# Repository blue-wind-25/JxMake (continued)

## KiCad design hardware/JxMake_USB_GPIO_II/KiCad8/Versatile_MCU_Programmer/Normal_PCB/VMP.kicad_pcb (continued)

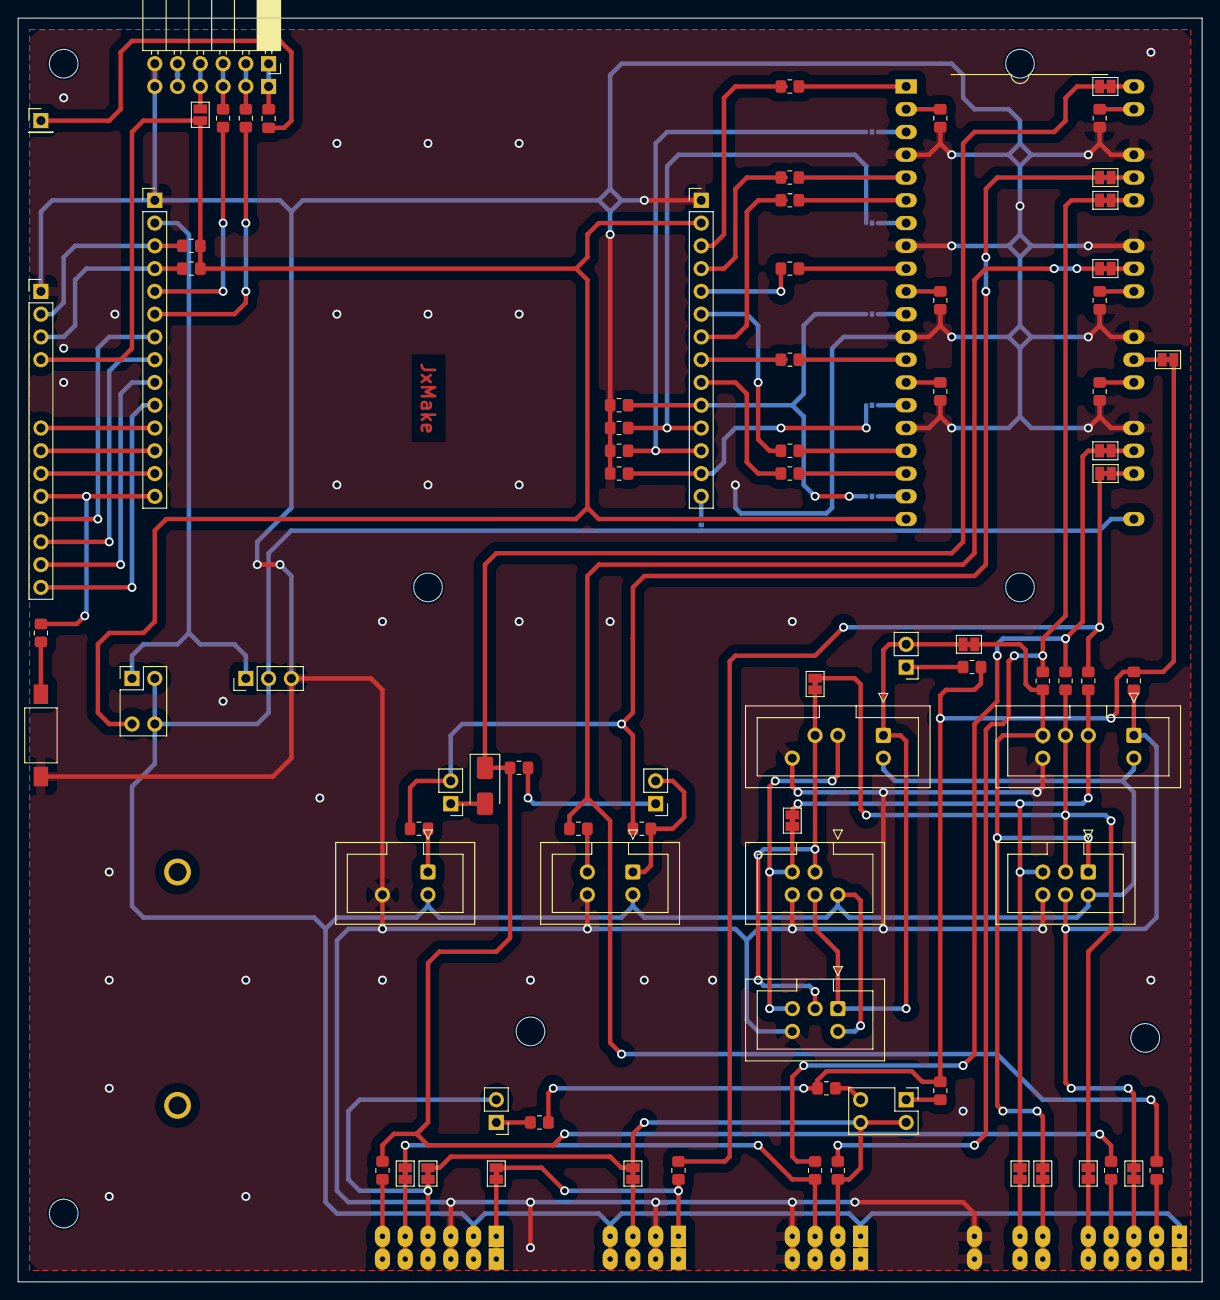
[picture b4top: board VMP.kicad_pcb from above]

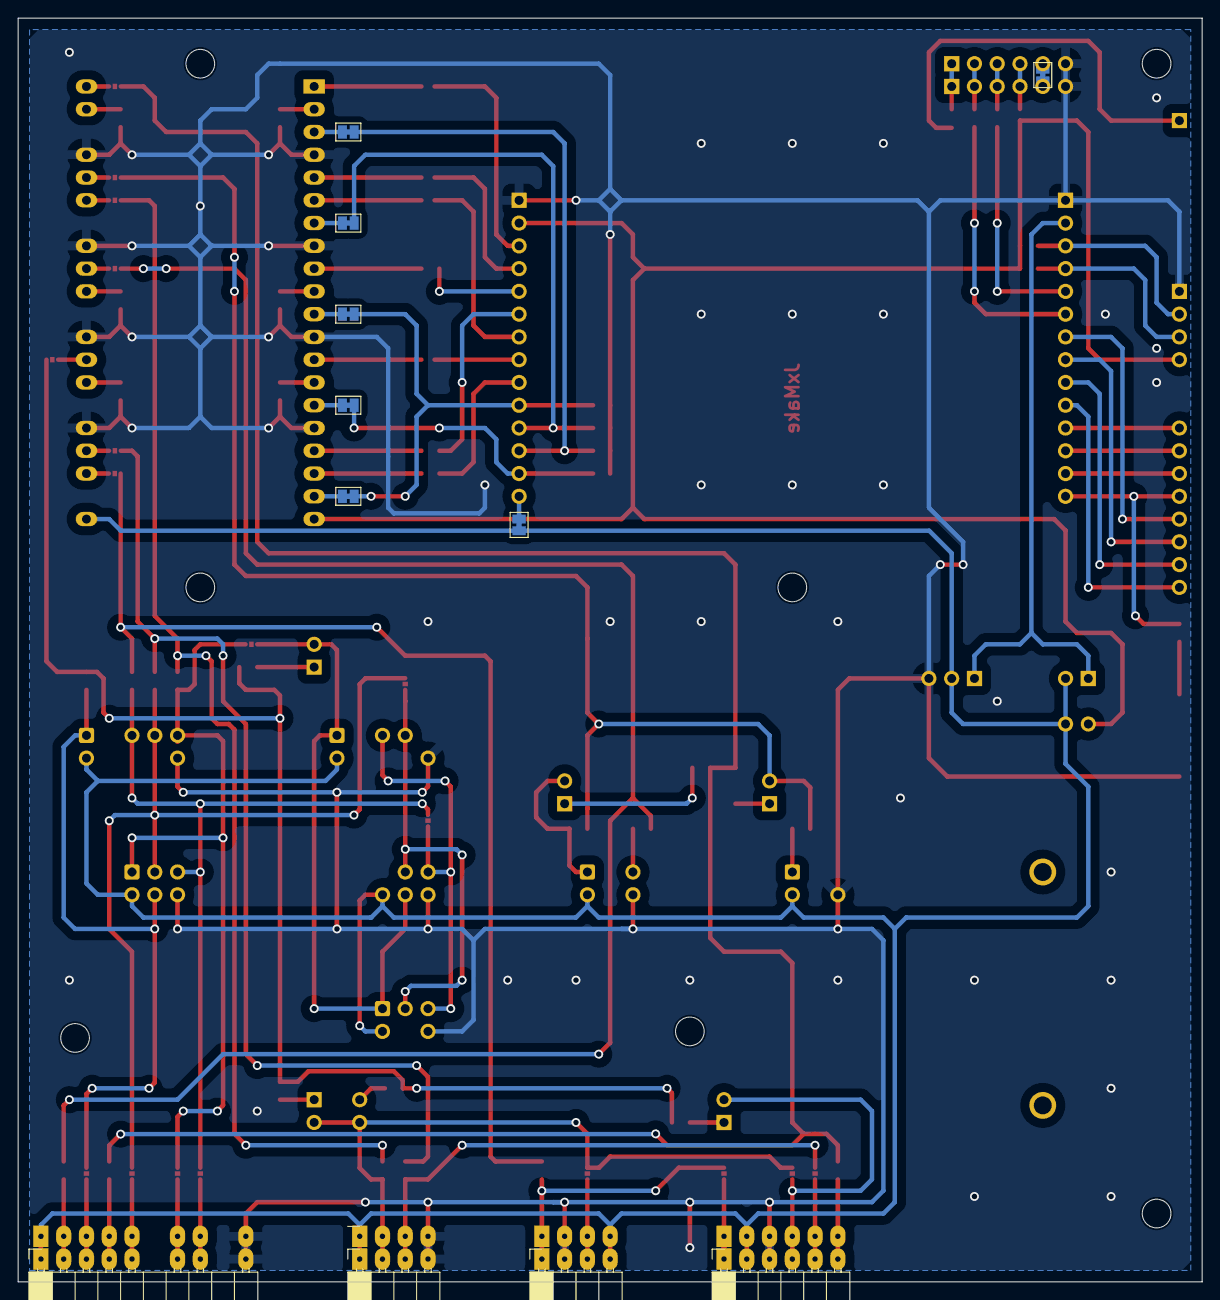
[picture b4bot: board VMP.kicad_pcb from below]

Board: 2 copper layers, 132.1 x 141.0 mm, 100 parts (11 on the bottom side), 97 nets.

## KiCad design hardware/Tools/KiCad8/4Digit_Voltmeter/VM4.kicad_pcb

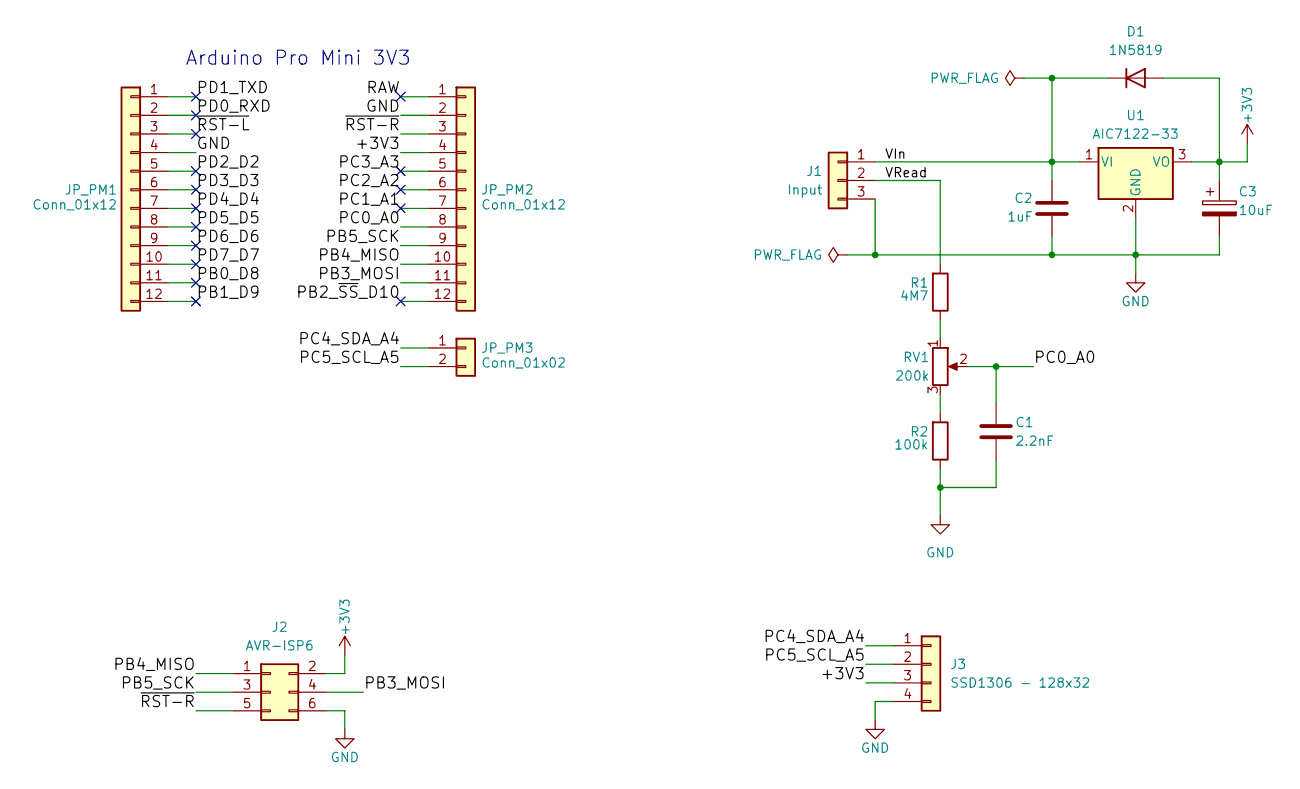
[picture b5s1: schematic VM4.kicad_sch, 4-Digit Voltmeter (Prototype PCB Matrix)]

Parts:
C1: 2.2nF; C_Disc_D4.7mm_W2.5mm_P5.00mm
C2: 1uF; C_Disc_D4.7mm_W2.5mm_P5.00mm
C3: 10uF; CP_Radial_Tantal_D5.0mm_P2.50mm
D1: 1N5819; D_DO-41_SOD81_P7.62mm_Horizontal
J1: Input; PinHeader_1x03_P2.54mm_Horizontal
J2: AVR-ISP6; IDC-Header_2x03_P2.54mm_Vertical
J3: SSD1306 - 128x32; PinHeader_1x04_P2.54mm_Vertical
JP_PM1, JP_PM2: Conn_01x12; PinHeader_1x12_P2.54mm_Vertical
JP_PM3: Conn_01x02; PinHeader_1x02_P2.54mm_Vertical
R1: 4M7; R_Axial_DIN0207_L6.3mm_D2.5mm_P10.16mm_Horizontal
R2: 100k; R_Axial_DIN0207_L6.3mm_D2.5mm_P10.16mm_Horizontal
RV1: 200k; Potentiometer_Bourns_3296W_Vertical
U1: AIC7122-33; TO-92L_Inline_Wide

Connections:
+3V3: C3.1, D1.2 (A), J2.2, J3.3, JP_PM2.4, U1.3 (VO)
/PB0_D8: JP_PM1.11
/PB1_D9: JP_PM1.12
/PB2_~SS_D10: JP_PM2.12
/PB3_MOSI: J2.4, JP_PM2.11
/PB4_MISO: J2.1, JP_PM2.10
/PB5_SCK: J2.3, JP_PM2.9
/PC0_A0: C1.1, JP_PM2.8, RV1.2
/PC1_A1: JP_PM2.7
/PC2_A2: JP_PM2.6
/PC3_A3: JP_PM2.5
/PC4_SDA_A4: J3.1, JP_PM3.1
/PC5_SCL_A5: J3.2, JP_PM3.2
/PD0_RXD: JP_PM1.2
/PD1_TXD: JP_PM1.1
/PD2_D2: JP_PM1.5
/PD3_D3: JP_PM1.6
/PD4_D4: JP_PM1.7
/PD5_D5: JP_PM1.8
/PD6_D6: JP_PM1.9
/PD7_D7: JP_PM1.10
/RAW: JP_PM2.1
/VIn: C2.1, D1.1 (K), J1.1, U1.1 (VI)
/VRead: J1.2, R1.2
/~RST-L: JP_PM1.3
/~RST-R: J2.5, JP_PM2.3
GND: C1.2, C2.2, C3.2, J1.3, J2.6, J3.4, JP_PM1.4, JP_PM2.2, R2.1, U1.2 (GND)
unnamed: R1.1, RV1.1
unnamed: R2.2, RV1.3

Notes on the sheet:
Arduino Pro Mini 3V3

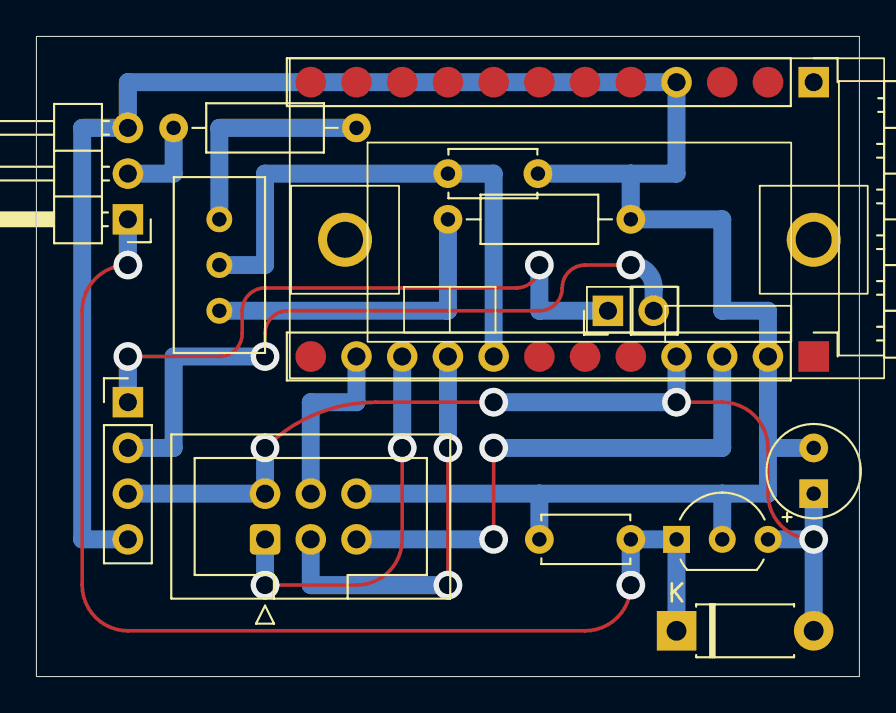
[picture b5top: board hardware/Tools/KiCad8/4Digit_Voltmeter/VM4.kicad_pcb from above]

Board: 2 copper layers, 45.7 x 35.6 mm, 14 parts (0 on the bottom side), 13 nets.

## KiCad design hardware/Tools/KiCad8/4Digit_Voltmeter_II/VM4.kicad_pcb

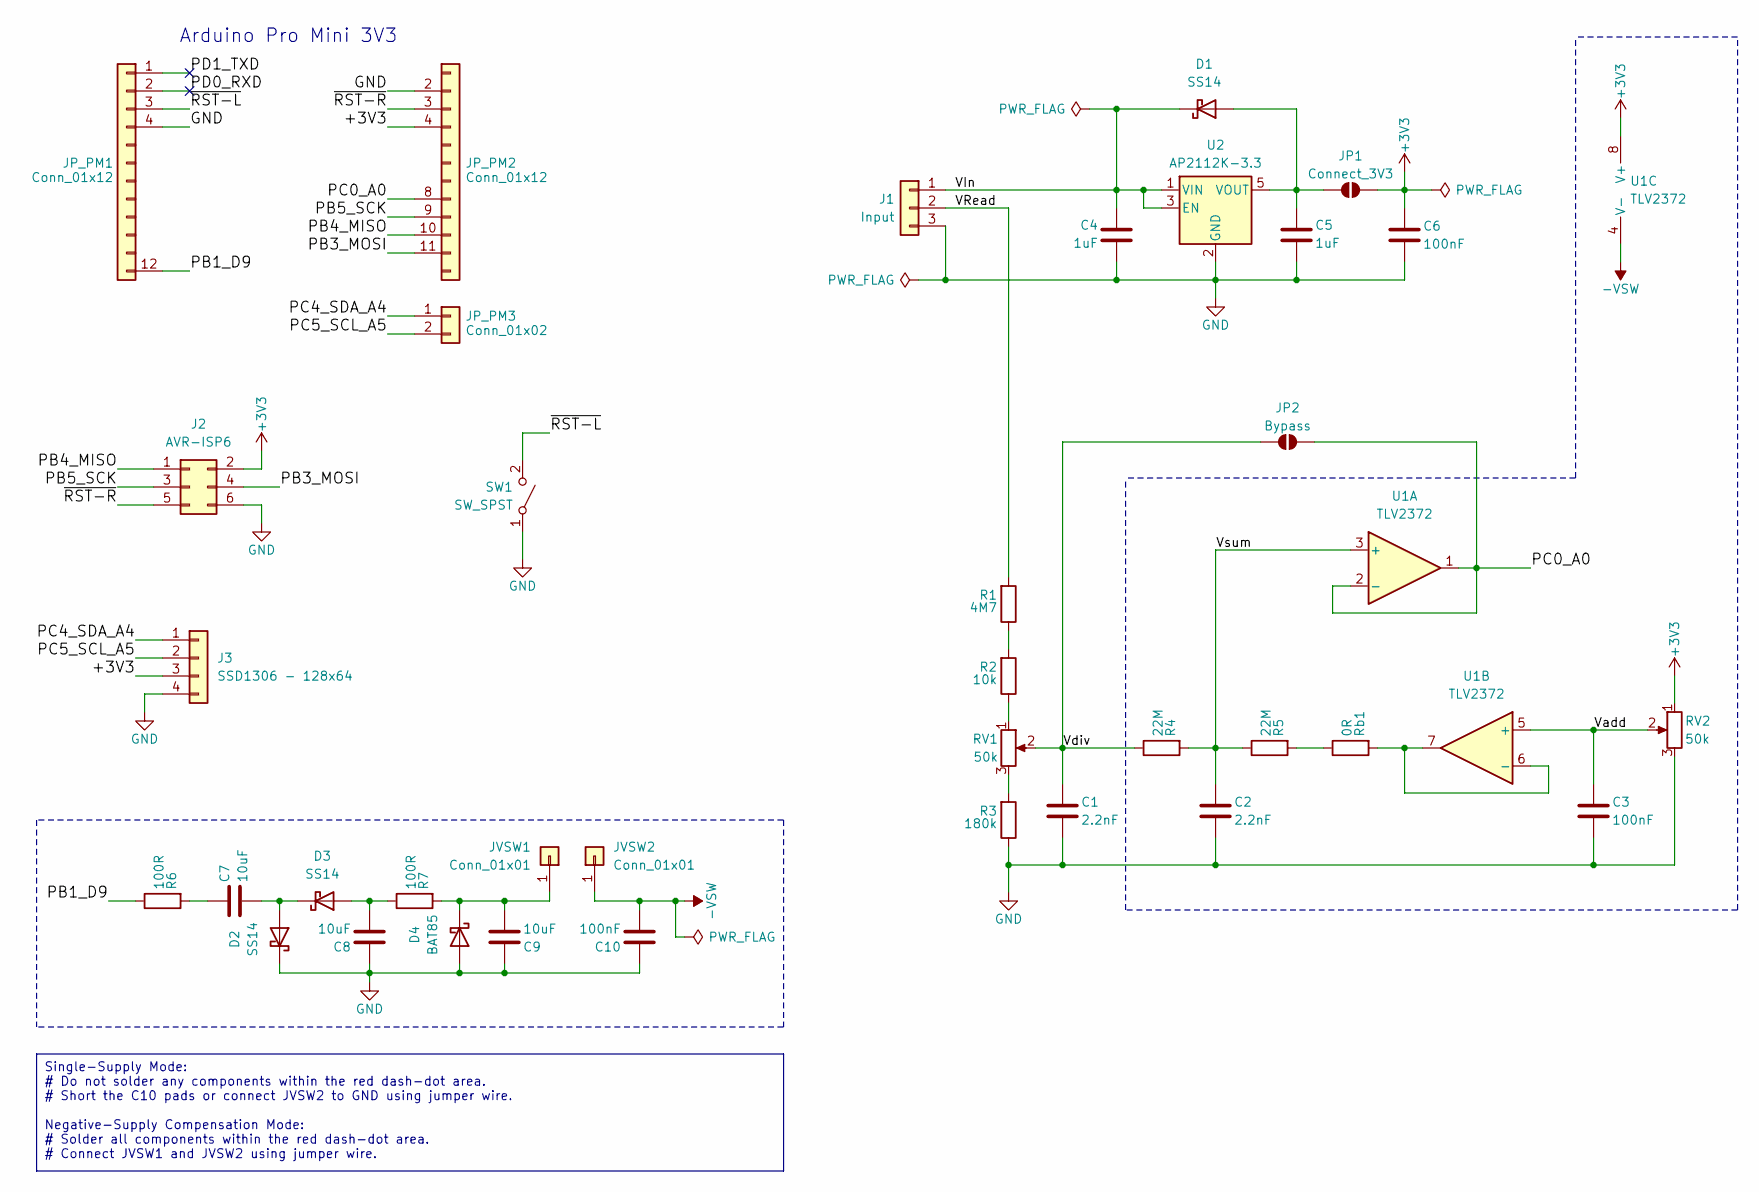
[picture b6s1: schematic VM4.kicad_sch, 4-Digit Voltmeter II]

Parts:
C1, C2: 2.2nF; C_0805_2012Metric_Pad1.18x1.45mm_HandSolder
C3, C6, C10: 100nF; C_0805_2012Metric_Pad1.18x1.45mm_HandSolder
C4, C5: 1uF; C_0805_2012Metric_Pad1.18x1.45mm_HandSolder
C7, C8, C9: 10uF; C_0805_2012Metric_Pad1.18x1.45mm_HandSolder
D1, D2, D3: SS14; D_SMA
D4: BAT85; D_SMA
J1: Input; PinHeader_1x03_P2.54mm_Horizontal
J2: AVR-ISP6; IDC-Header_2x03_P2.54mm_Horizontal
J3: SSD1306 - 128x64; PinHeader_1x04_P2.54mm_Vertical
JP1: Connect_3V3; SolderJumper-2_P1.3mm_Open_Pad1.0x1.5mm
JP2: Bypass; SolderJumper-2_P1.3mm_Open_Pad1.0x1.5mm
JP_PM1, JP_PM2: Conn_01x12; PinHeader_1x12_P2.54mm_Vertical
JP_PM3: Conn_01x02; PinHeader_1x02_P2.54mm_Vertical
JVSW1, JVSW2: Conn_01x01; PinHeader_1x01_P1.00mm_Vertical
R1: 4M7; R_0805_2012Metric_Pad1.20x1.40mm_HandSolder
R2: 10k; R_0805_2012Metric_Pad1.20x1.40mm_HandSolder
R3: 180k; R_0805_2012Metric_Pad1.20x1.40mm_HandSolder
R4, R5: 22M; R_0805_2012Metric_Pad1.20x1.40mm_HandSolder
R6, R7: 100R; R_0805_2012Metric_Pad1.20x1.40mm_HandSolder
RV1, RV2: 50k; Potentiometer_Bourns_3296W_Vertical
Rb1: 0R; R_0805_2012Metric_Pad1.20x1.40mm_HandSolder
SW1: SW_SPST; SW_PUSH_1P1T_6x3.5mm_H4.3_APEM_MJTP1243
U1: TLV2372; SOIC-8_3.9x4.9mm_P1.27mm
U2: AP2112K-3.3; SOT-23-5

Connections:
+3V3: C6.1, J2.2, J3.3, JP1.2 (B), JP_PM2.4, RV2.1, U1.8 (V+)
-VSW: C10.2, JVSW2.1, U1.4 (V-)
/PB1_D9: JP_PM1.12, R6.1
/PB3_MOSI: J2.4, JP_PM2.11
/PB4_MISO: J2.1, JP_PM2.10
/PB5_SCK: J2.3, JP_PM2.9
/PC0_A0: JP2.2 (B), JP_PM2.8, U1.1, U1.2 (-)
/PC4_SDA_A4: J3.1, JP_PM3.1
/PC5_SCL_A5: J3.2, JP_PM3.2
/PD0_RXD: JP_PM1.2
/PD1_TXD: JP_PM1.1
/VIn: C4.1, D1.1 (K), J1.1, U2.1 (VIN), U2.3 (EN)
/VRead: J1.2, R1.2
/Vadd: C3.1, RV2.2, U1.5 (+)
/Vdiv: C1.1, JP2.1 (A), R4.1, RV1.2
/Vsum: C2.1, R4.2, R5.1, U1.3 (+)
/~RST-L: JP_PM1.3, SW1.2 (B)
/~RST-R: J2.5, JP_PM2.3
GND: C1.2, C2.2, C3.2, C4.2, C5.2, C6.2, C8.1, C9.1, C10.1, D2.1 (K), D4.2 (A), J1.3, J2.6, J3.4, JP_PM1.4, JP_PM2.2, R3.1, RV2.3, SW1.1 (A), U2.2 (GND)
unnamed: C7.1, R6.2
unnamed: C5.1, D1.2 (A), JP1.1 (A), U2.5 (VOUT)
unnamed: C7.2, D2.2 (A), D3.1 (K)
unnamed: C8.2, D3.2 (A), R7.1
unnamed: C9.2, D4.1 (K), JVSW1.1, R7.2
unnamed: R1.1, R2.2
unnamed: R2.1, RV1.1
unnamed: R3.2, RV1.3
unnamed: R5.2, Rb1.1
unnamed: Rb1.2, U1.6 (-), U1.7

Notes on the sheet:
Single-Supply Mode: # Do not solder any components within the red dash-dot area. # Short the C10 pads or connect JVSW2 to GND using jumper wire. Negative-Supply Compensation Mode: # Solder all components within the red dash-dot area. # Connect JVSW1 and JVSW2 using jumper wire.
Arduino Pro Mini 3V3

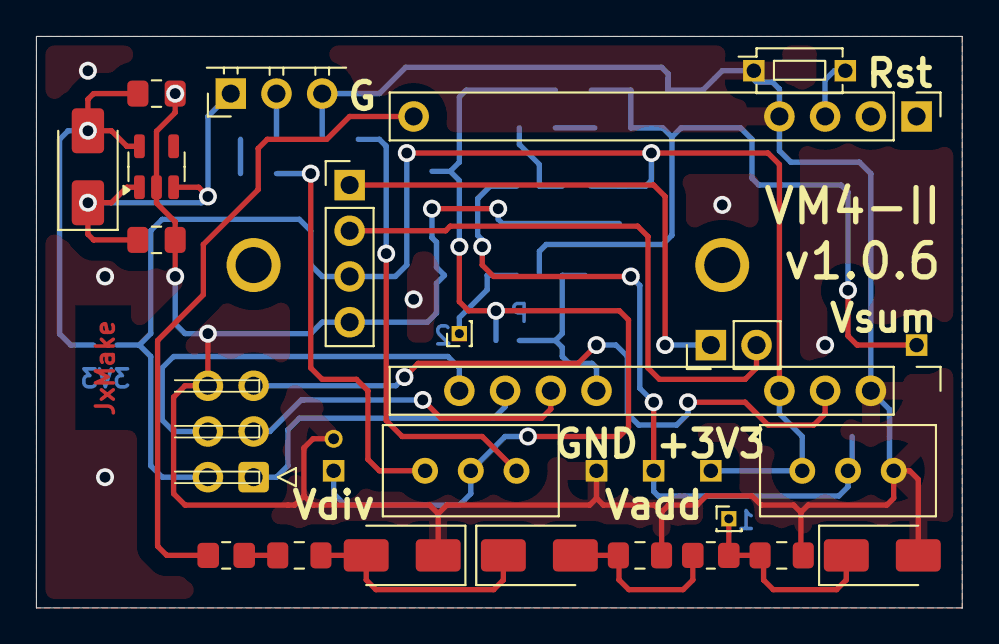
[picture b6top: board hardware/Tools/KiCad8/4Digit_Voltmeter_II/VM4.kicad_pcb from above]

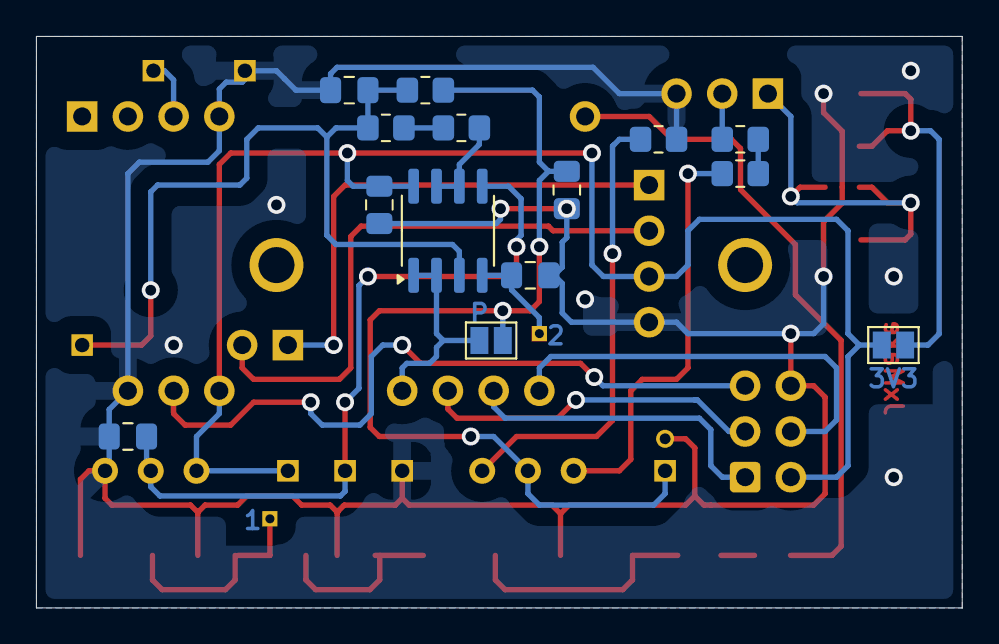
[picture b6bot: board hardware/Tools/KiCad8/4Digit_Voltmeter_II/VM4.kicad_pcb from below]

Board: 2 copper layers, 51.4 x 31.8 mm, 37 parts (14 on the bottom side), 27 nets.

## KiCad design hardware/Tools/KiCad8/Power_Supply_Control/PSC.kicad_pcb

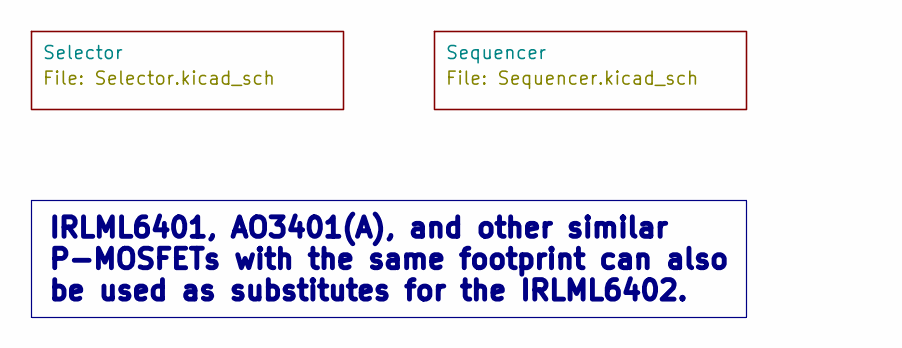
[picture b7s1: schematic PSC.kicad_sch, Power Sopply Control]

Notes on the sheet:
IRLML6401, AO3401(A), and other similar P-MOSFETs with the same footprint can also be used as substitutes for the IRLML6402.

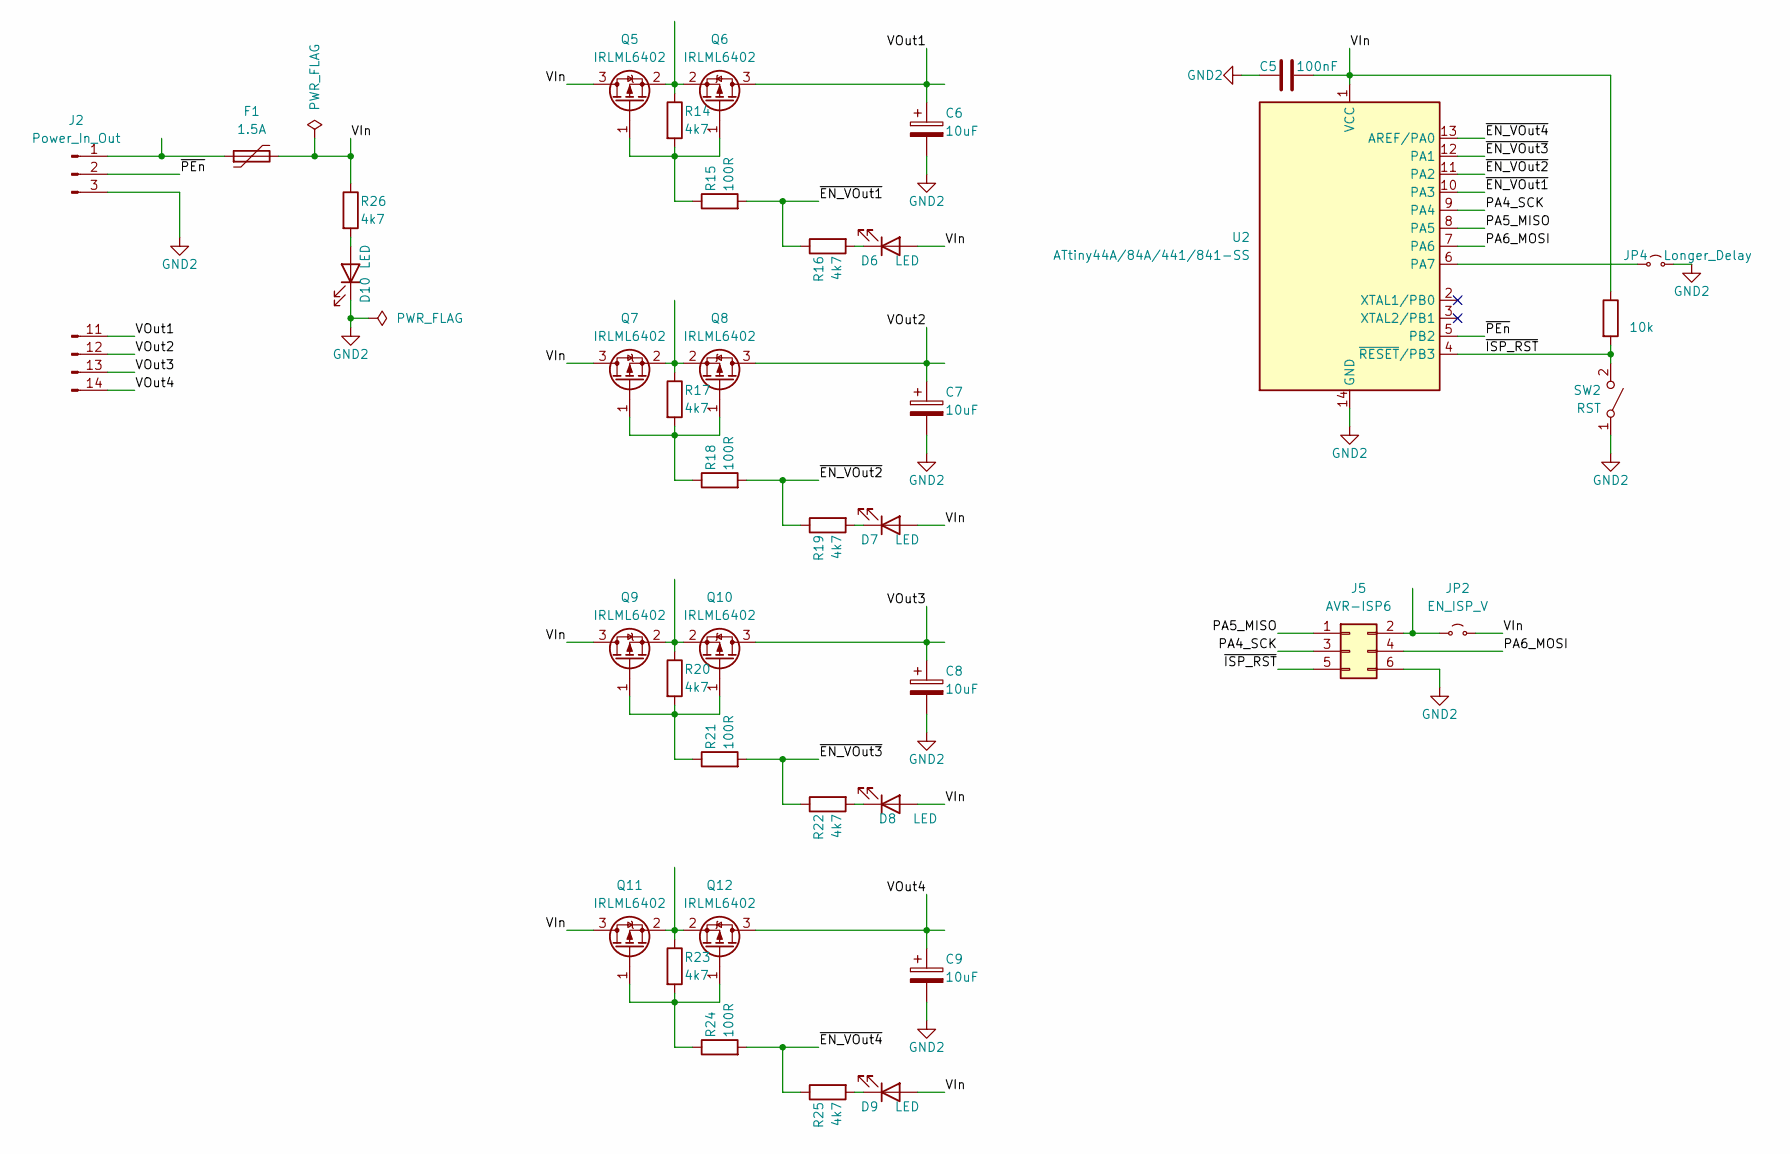
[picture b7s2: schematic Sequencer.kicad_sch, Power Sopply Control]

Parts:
C5: 100nF; C_0805_2012Metric_Pad1.18x1.45mm_HandSolder
C6, C7, C8, C9: 10uF; CP_EIA-3528-21_Kemet-B_Pad1.50x2.35mm_HandSolder
D6, D7, D8, D9, D10: LED; LED_0805_2012Metric_Pad1.15x1.40mm_HandSolder
F1: 1.5A; R_4020_10251Metric_Pad1.65x5.30mm_HandSolder
J2: Power_In_Out; PinHeader_1x14_P2.54mm_Vertical
J5: AVR-ISP6; IDC-Header_2x03_P2.54mm_Horizontal
JP2: EN_ISP_V; SolderJumper-2_P1.3mm_Open_RoundedPad1.0x1.5mm
JP4: Longer_Delay; SolderJumper-2_P1.3mm_Open_RoundedPad1.0x1.5mm
Q5, Q6, Q7, Q8, Q9, Q10, Q11, Q12: IRLML6402; SOT-23_Handsoldering
R13: 10k; R_0805_2012Metric_Pad1.20x1.40mm_HandSolder
R14, R16, R17, R19, R20, R22, R23, R25, R26: 4k7; R_0805_2012Metric_Pad1.20x1.40mm_HandSolder
R15, R18, R21, R24: 100R; R_0805_2012Metric_Pad1.20x1.40mm_HandSolder
SW2: RST; SW_SPST_CK_RS282G05A3
U2: ATtiny44A/84A/441/841-SS; SOIC-14_3.9x8.7mm_P1.27mm

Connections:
/Sequencer/PA4_SCK: J5.3, U2.9 (PA4)
/Sequencer/PA5_MISO: J5.1, U2.8 (PA5)
/Sequencer/PA6_MOSI: J5.4, U2.7 (PA6)
/Sequencer/VIn: C5.1, D6.2 (A), D7.2 (A), D8.2 (A), D9.2 (A), F1.2, JP2.2 (B), Q5.3 (D), Q7.3 (D), Q9.3 (D), Q11.3 (D), R13.1, R26.1, U2.1 (VCC)
/Sequencer/VOut1: C6.1, J2.11, Q6.3 (D)
/Sequencer/VOut2: C7.1, J2.12, Q8.3 (D)
/Sequencer/VOut3: C8.1, J2.13, Q10.3 (D)
/Sequencer/VOut4: C9.1, J2.14, Q12.3 (D)
/Sequencer/~EN_VOut1: R15.2, R16.1, U2.10 (PA3)
/Sequencer/~EN_VOut2: R18.2, R19.1, U2.11 (PA2)
/Sequencer/~EN_VOut3: R21.2, R22.1, U2.12 (PA1)
/Sequencer/~EN_VOut4: R24.2, R25.1, U2.13 (AREF/PA0)
/Sequencer/~ISP_RST: J5.5, R13.2, SW2.2 (B), U2.4 (~RESET/PB3)
/Sequencer/~PEn: J2.2, U2.5 (PB2)
GND2: C5.2, C6.2, C7.2, C8.2, C9.2, D10.1 (K), J2.3, J5.6, JP4.2 (B), SW2.1 (A), U2.14 (GND)
unnamed: D6.1 (K), R16.2
unnamed: D7.1 (K), R19.2
unnamed: D8.1 (K), R22.2
unnamed: D9.1 (K), R25.2
unnamed: D10.2 (A), R26.2
unnamed: F1.1, J2.1
unnamed: J5.2, JP2.1 (A)
unnamed: JP4.1 (A), U2.6 (PA7)
unnamed: Q5.1 (G), Q6.1 (G), R14.2, R15.1
unnamed: Q5.2 (S), Q6.2 (S), R14.1
unnamed: Q7.1 (G), Q8.1 (G), R17.2, R18.1
unnamed: Q7.2 (S), Q8.2 (S), R17.1
unnamed: Q9.1 (G), Q10.1 (G), R20.2, R21.1
unnamed: Q9.2 (S), Q10.2 (S), R20.1
unnamed: Q11.1 (G), Q12.1 (G), R23.2, R24.1
unnamed: Q11.2 (S), Q12.2 (S), R23.1

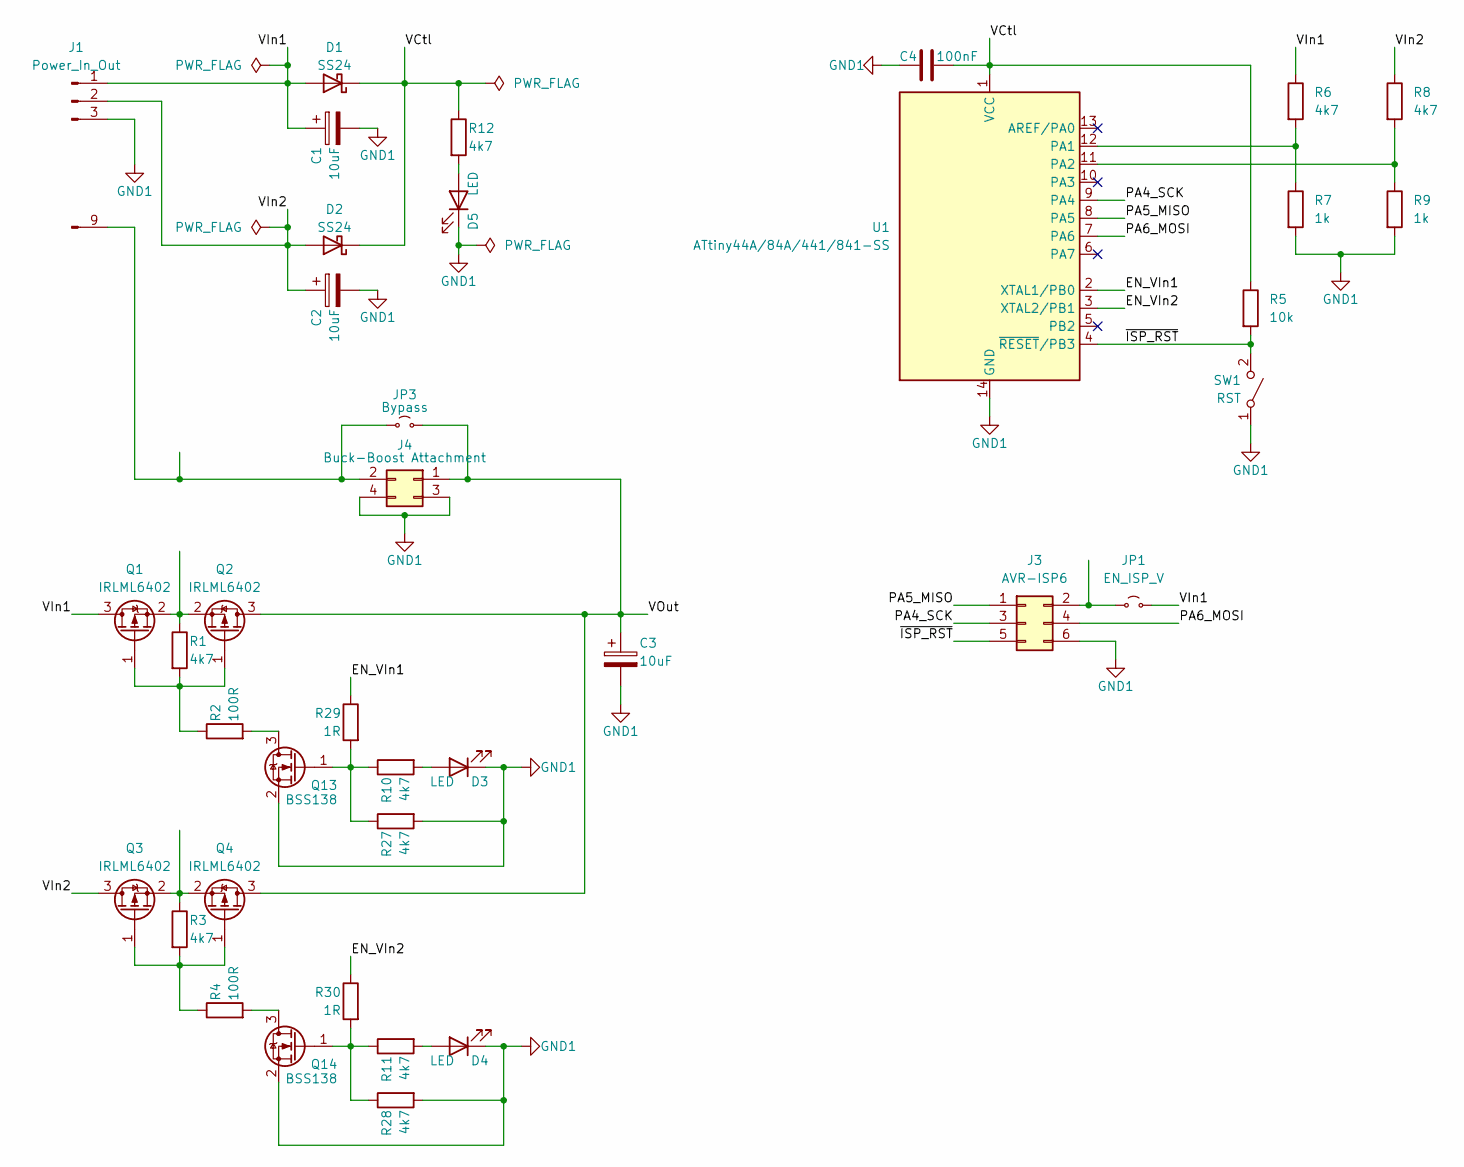
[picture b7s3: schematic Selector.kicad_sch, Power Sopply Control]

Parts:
C1, C2, C3: 10uF; CP_EIA-3528-21_Kemet-B_Pad1.50x2.35mm_HandSolder
C4: 100nF; C_0805_2012Metric_Pad1.18x1.45mm_HandSolder
D1, D2: SS24; D_SMA_Handsoldering
D3, D4, D5: LED; LED_0805_2012Metric_Pad1.15x1.40mm_HandSolder
J1: Power_In_Out; PinHeader_1x09_P2.54mm_Vertical
J3: AVR-ISP6; IDC-Header_2x03_P2.54mm_Horizontal
J4: Buck-Boost Attachment; PinHeader_2x02_P2.54mm_Vertical
JP1: EN_ISP_V; SolderJumper-2_P1.3mm_Open_RoundedPad1.0x1.5mm
JP3: Bypass; SolderJumper-2_P1.3mm_Open_RoundedPad1.0x1.5mm
Q1, Q2, Q3, Q4: IRLML6402; SOT-23_Handsoldering
Q13, Q14: BSS138; SOT-23_Handsoldering
R1, R3, R6, R8, R10, R11, R12, R27, R28: 4k7; R_0805_2012Metric_Pad1.20x1.40mm_HandSolder
R2, R4: 100R; R_0805_2012Metric_Pad1.20x1.40mm_HandSolder
R5: 10k; R_0805_2012Metric_Pad1.20x1.40mm_HandSolder
R7, R9: 1k; R_0805_2012Metric_Pad1.20x1.40mm_HandSolder
R29, R30: 1R; R_0805_2012Metric_Pad1.20x1.40mm_HandSolder
SW1: RST; SW_SPST_CK_RS282G05A3
U1: ATtiny44A/84A/441/841-SS; SOIC-14_3.9x8.7mm_P1.27mm

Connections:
/Selector/EN_VIn1: R29.1, U1.2 (XTAL1/PB0)
/Selector/EN_VIn2: R30.1, U1.3 (XTAL2/PB1)
/Selector/PA4_SCK: J3.3, U1.9 (PA4)
/Selector/PA5_MISO: J3.1, U1.8 (PA5)
/Selector/PA6_MOSI: J3.4, U1.7 (PA6)
/Selector/VCtl: C4.1, D1.1 (K), D2.1 (K), R5.1, R12.1, U1.1 (VCC)
/Selector/VIn1: C1.1, D1.2 (A), J1.1, JP1.2 (B), Q1.3 (D), R6.1
/Selector/VIn2: C2.1, D2.2 (A), J1.2, Q3.3 (D), R8.1
/Selector/VOut: C3.1, J4.1, JP3.2 (B), Q2.3 (D), Q4.3 (D)
/Selector/~ISP_RST: J3.5, R5.2, SW1.2 (B), U1.4 (~RESET/PB3)
GND1: C1.2, C2.2, C3.2, C4.2, D3.1 (K), D4.1 (K), D5.1 (K), J1.3, J3.6, J4.3, J4.4, Q13.2 (S), Q14.2 (S), R7.2, R9.2, R27.2, R28.2, SW1.1 (A), U1.14 (GND)
unnamed: D3.2 (A), R10.2
unnamed: D4.2 (A), R11.2
unnamed: D5.2 (A), R12.2
unnamed: J1.9, J4.2, JP3.1 (A)
unnamed: J3.2, JP1.1 (A)
unnamed: Q1.1 (G), Q2.1 (G), R1.2, R2.1
unnamed: Q1.2 (S), Q2.2 (S), R1.1
unnamed: Q3.1 (G), Q4.1 (G), R3.2, R4.1
unnamed: Q3.2 (S), Q4.2 (S), R3.1
unnamed: Q13.3 (D), R2.2
unnamed: Q13.1 (G), R10.1, R27.1, R29.2
unnamed: Q14.3 (D), R4.2
unnamed: Q14.1 (G), R11.1, R28.1, R30.2
unnamed: R6.2, R7.1, U1.12 (PA1)
unnamed: R8.2, R9.1, U1.11 (PA2)

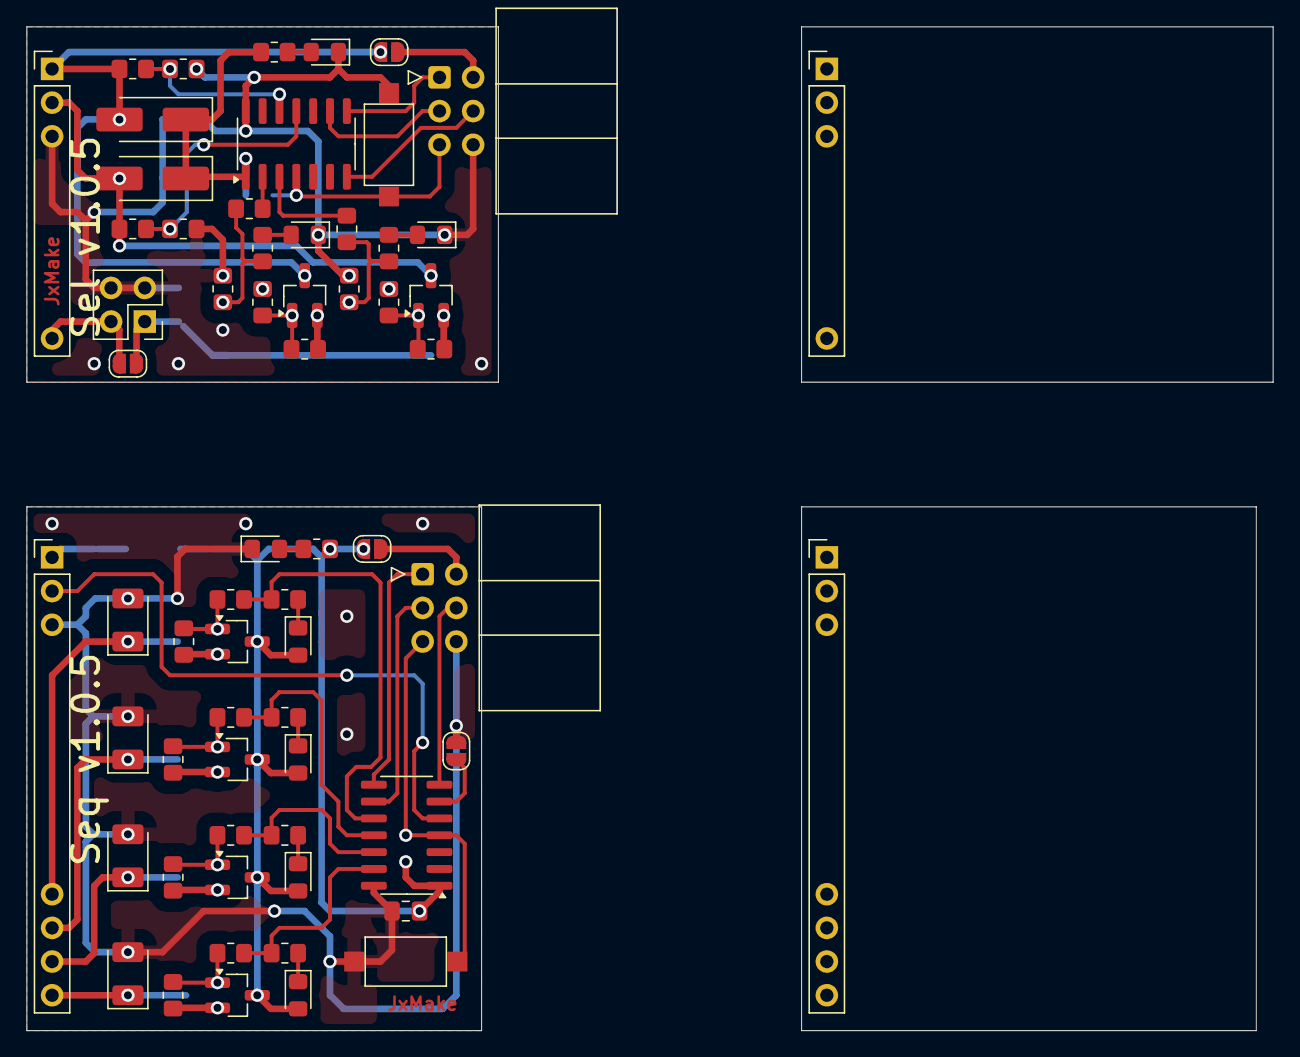
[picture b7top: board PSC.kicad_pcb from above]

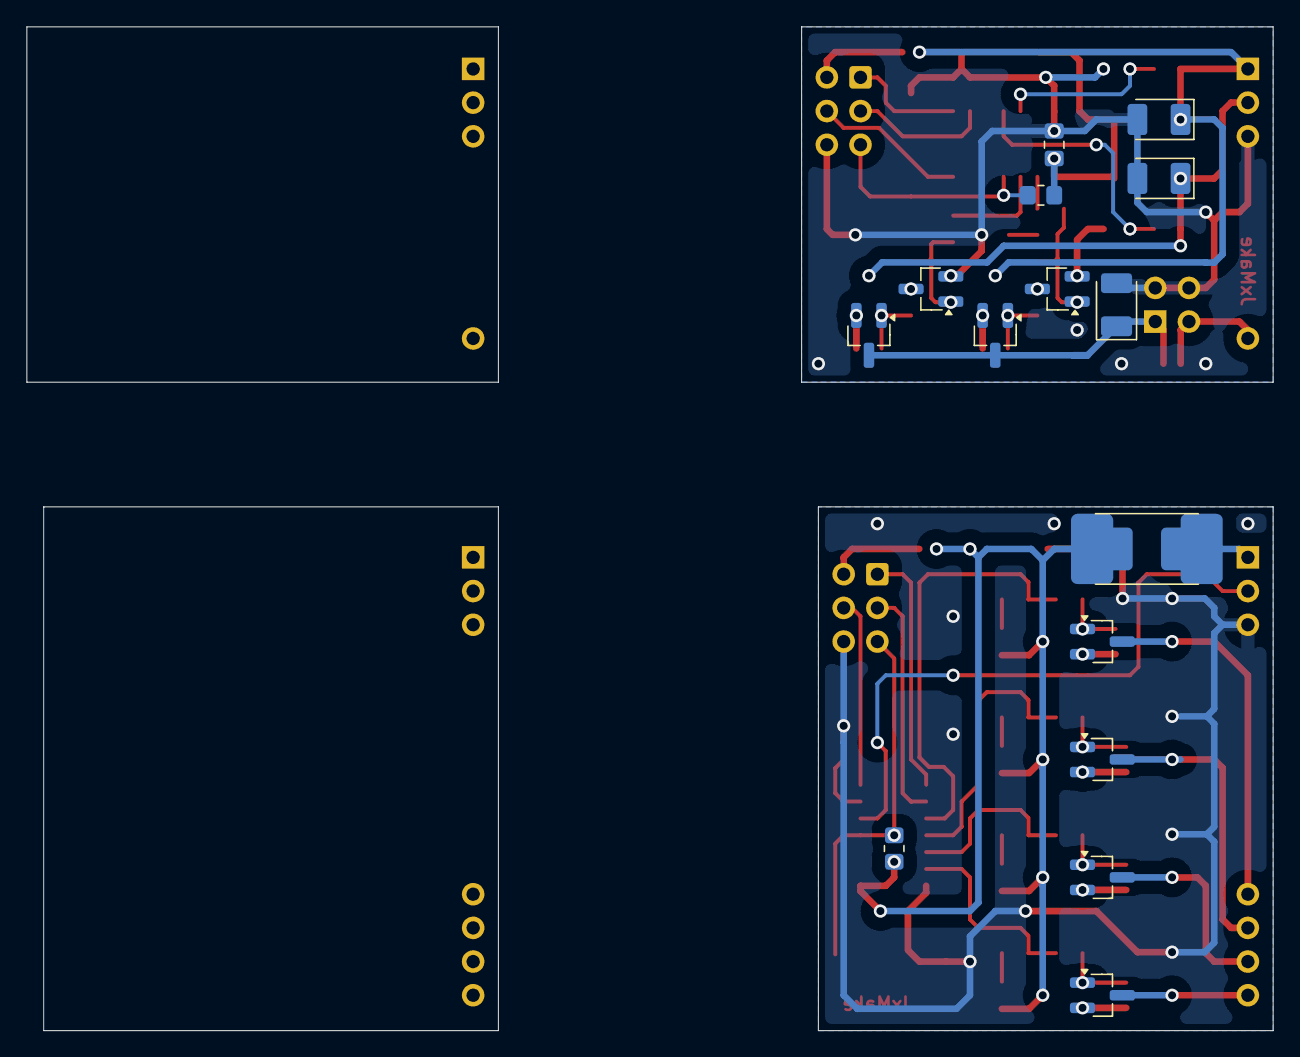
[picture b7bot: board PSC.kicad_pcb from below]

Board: 2 copper layers, 94.0 x 75.7 mm, 79 parts (15 on the bottom side), 57 nets.

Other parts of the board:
J1R: Power_In_Out; PinHeader_1x09_P2.54mm_Vertical
J2R: Power_In_Out; PinHeader_1x14_P2.54mm_Vertical
